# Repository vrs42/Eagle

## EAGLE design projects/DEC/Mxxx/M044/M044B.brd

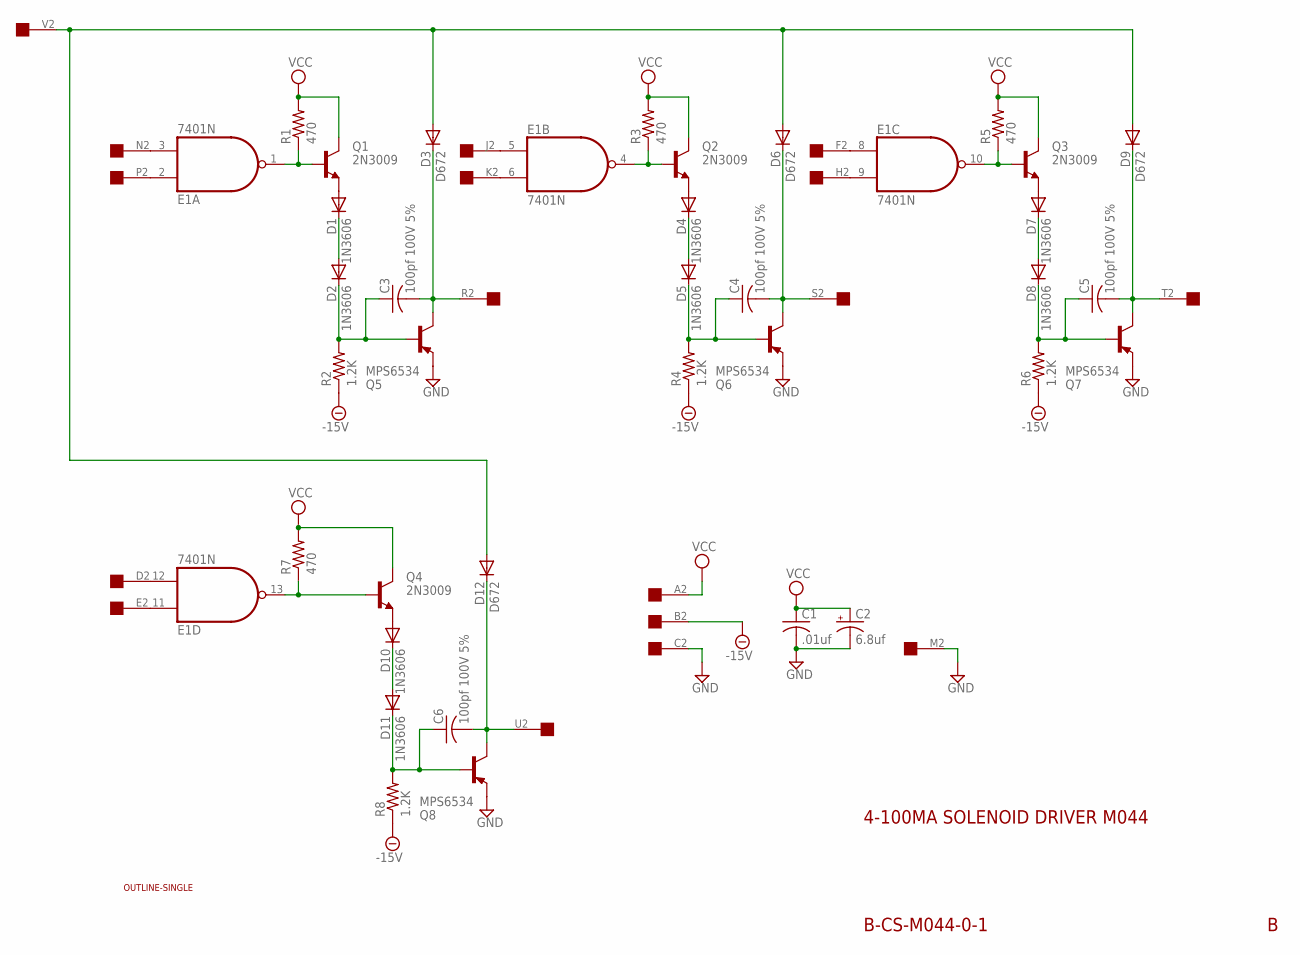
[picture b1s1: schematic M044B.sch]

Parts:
C1: .01uf; C050-025X075
C2: 6.8uf; E15-5
C3, C4, C5, C6: 100pf 100V 5%; C050-025X075
D1, D2, D4, D5, D7, D8, D10, D11: 1N3606; DO35-10
D3, D6, D9, D12: D672; DO35-10
E1: 7401N; DIL14
Q1, Q2, Q3, Q4: 2N3009; TO39
Q5, Q6, Q7, Q8: MPS6534; TO39
R1, R3, R5, R7: 470; 0207/10
R2, R4, R6, R8: 1.2K; 0207/10
U$1: OUTLINE-SINGLE; SINGLE
U$2: EDGE-1; EDGE-CON1

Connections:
-15V: R2.1, R4.1, R6.1, R8.1, U$2.B2
GND: C1.2, C2.-, E1.7 (GND), Q5.1 (E), Q6.1 (E), Q7.1 (E), Q8.1 (E), U$2.C2, U$2.M2
unnamed: E1.3 (I1), U$2.N2
unnamed: E1.2 (I0), U$2.P2
unnamed: E1.1 (O), Q1.2 (B), R1.1
unnamed: D1.A, Q1.1 (E)
unnamed: D1.C, D2.A
unnamed: C3.1, D2.C, Q5.2 (B), R2.2
unnamed: C3.2, D3.C, Q5.3 (C), U$2.R2
unnamed: D3.A, D6.A, D9.A, D12.A, U$2.V2
unnamed: E1.4 (O), Q2.2 (B), R3.1
unnamed: D4.A, Q2.1 (E)
unnamed: D4.C, D5.A
unnamed: C4.1, D5.C, Q6.2 (B), R4.2
unnamed: C4.2, D6.C, Q6.3 (C), U$2.S2
unnamed: E1.5 (I0), U$2.J2
unnamed: E1.6 (I1), U$2.K2
unnamed: E1.10 (O), Q3.2 (B), R5.1
unnamed: D7.A, Q3.1 (E)
unnamed: D7.C, D8.A
unnamed: C5.1, D8.C, Q7.2 (B), R6.2
unnamed: C5.2, D9.C, Q7.3 (C), U$2.T2
unnamed: E1.13 (O), Q4.2 (B), R7.1
unnamed: E1.9 (I1), U$2.H2
unnamed: E1.8 (I0), U$2.F2
unnamed: D10.A, Q4.1 (E)
unnamed: D10.C, D11.A
unnamed: C6.1, D11.C, Q8.2 (B), R8.2
unnamed: C6.2, D12.C, Q8.3 (C), U$2.U2
unnamed: E1.11 (I0), U$2.E2
unnamed: E1.12 (I1), U$2.D2
VCC: C1.1, C2.+, E1.14 (VCC), Q1.3 (C), Q2.3 (C), Q3.3 (C), Q4.3 (C), R1.2, R3.2, R5.2, R7.2, U$2.A2

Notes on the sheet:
4-100MA SOLENOID DRIVER M044
B-CS-M044-0-1

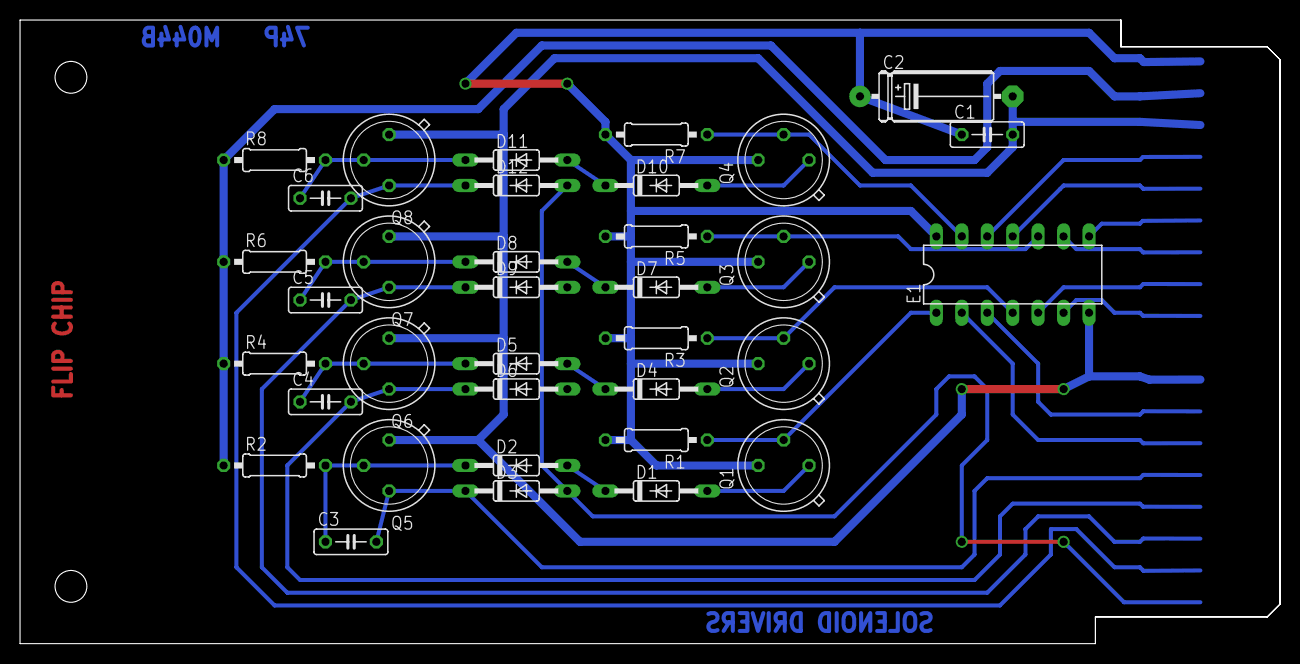
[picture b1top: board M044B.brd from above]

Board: 2 copper layers, 125.7 x 62.2 mm, 37 parts (0 on the bottom side), 32 nets.

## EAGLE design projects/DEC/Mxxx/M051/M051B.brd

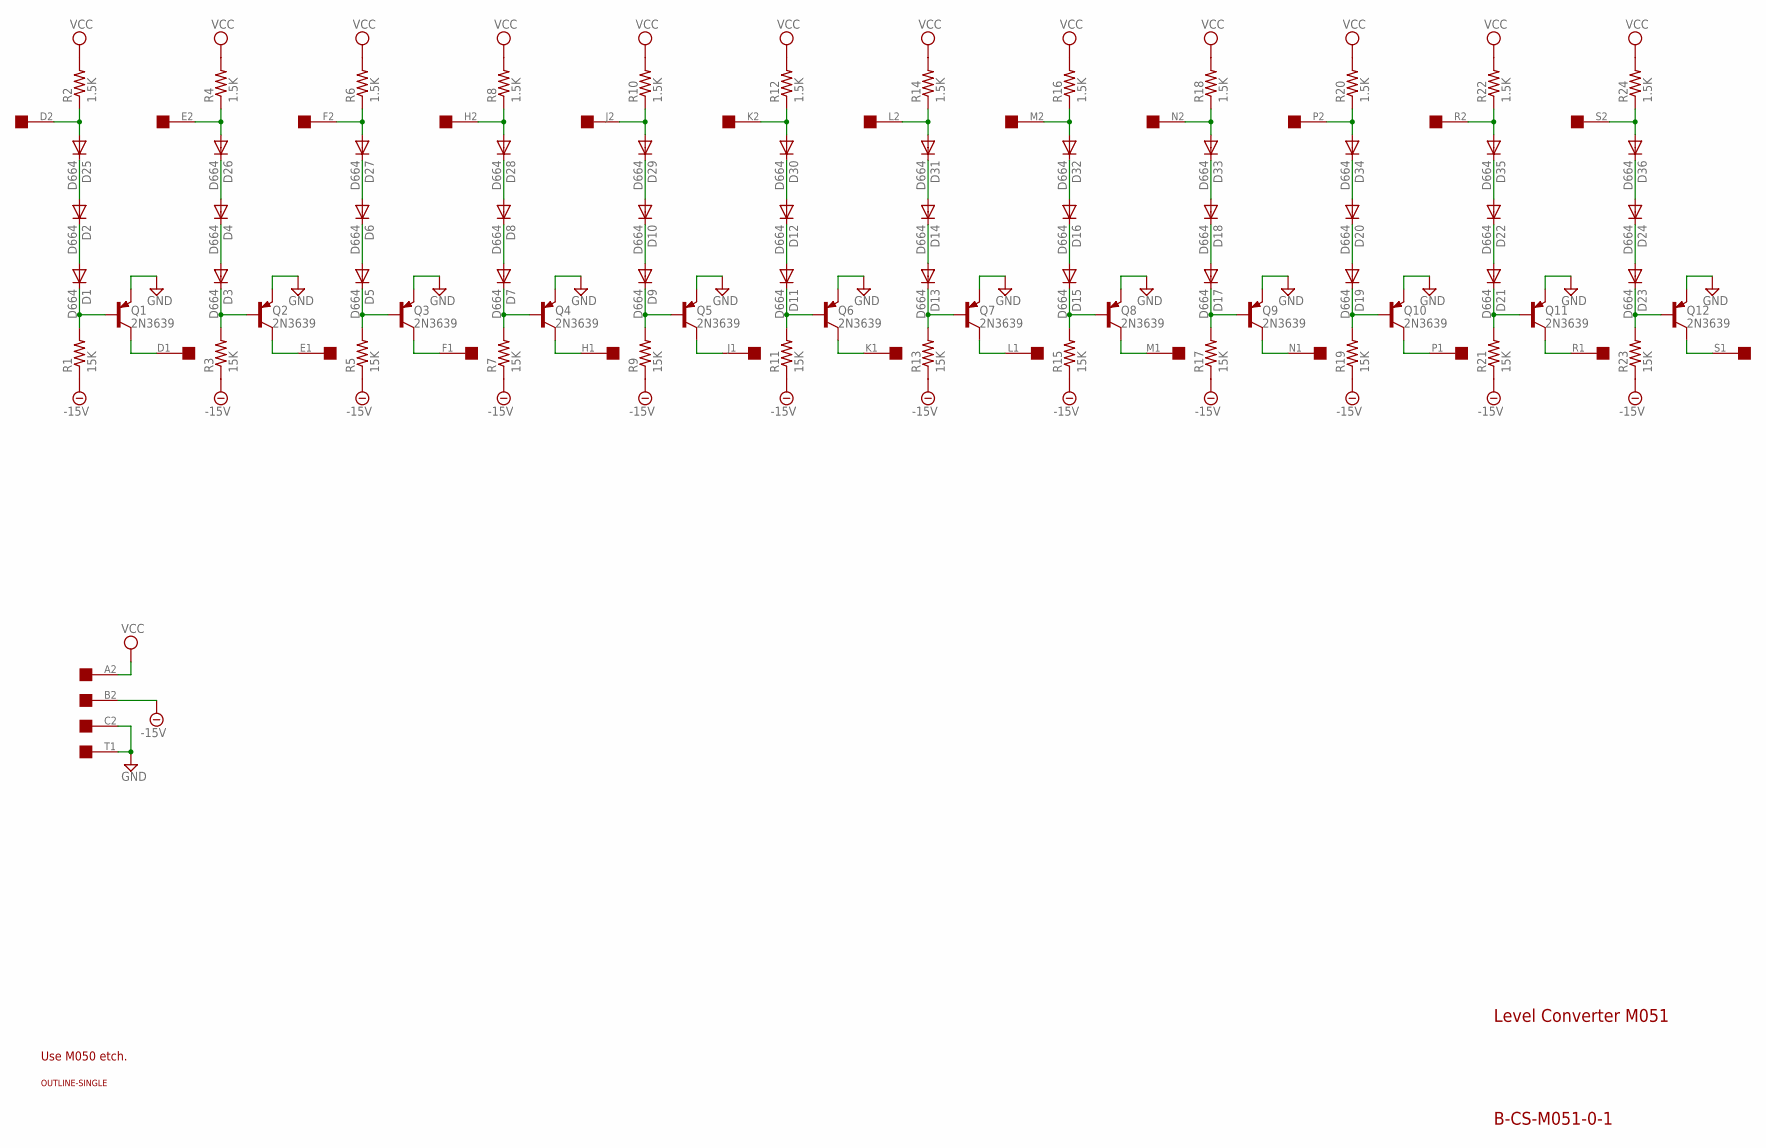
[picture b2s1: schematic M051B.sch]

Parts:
D1, D2, D3, D4, D5, D6, D7, D8, D9, D10, D11, D12, D13, D14, D15, D16, D17, D18, D19, D20, D21, D22, D23, D24, D25, D26, D27, D28, D29, D30, D31, D32, D33, D34, D35, D36: D664; DO35-10
Q1, Q2, Q3, Q4, Q5, Q6, Q7, Q8, Q9, Q10, Q11, Q12: 2N3639; TO5
R1, R3, R5, R7, R9, R11, R13, R15, R17, R19, R21, R23: 15K; 0207/10
R2, R4, R6, R8, R10, R12, R14, R16, R18, R20, R22, R24: 1.5K; 0207/10
U$1: OUTLINE-SINGLE; SINGLE
U$2: SINGLE; EDGE-CON2

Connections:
-15V: R1.1, R3.1, R5.1, R7.1, R9.1, R11.1, R13.1, R15.1, R17.1, R19.1, R21.1, R23.1, U$2.B2
D7: D6.A, D27.C
GND: Q1.1 (E), Q2.1 (E), Q3.1 (E), Q4.1 (E), Q5.1 (E), Q6.1 (E), Q7.1 (E), Q8.1 (E), Q9.1 (E), Q10.1 (E), Q11.1 (E), Q12.1 (E), U$2.C2, U$2.T1
unnamed: D25.A, R2.1, U$2.D2
unnamed: D2.A, D25.C
unnamed: D1.A, D2.C
unnamed: D1.C, Q1.2 (B), R1.2
unnamed: Q1.3 (C), U$2.D1
unnamed: D26.A, R4.1, U$2.E2
unnamed: D4.A, D26.C
unnamed: D3.A, D4.C
unnamed: D3.C, Q2.2 (B), R3.2
unnamed: Q2.3 (C), U$2.E1
unnamed: D27.A, R6.1, U$2.F2
unnamed: D5.A, D6.C
unnamed: D5.C, Q3.2 (B), R5.2
unnamed: Q3.3 (C), U$2.F1
unnamed: D28.A, R8.1, U$2.H2
unnamed: D8.A, D28.C
unnamed: D7.A, D8.C
unnamed: D7.C, Q4.2 (B), R7.2
unnamed: Q4.3 (C), U$2.H1
unnamed: D29.A, R10.1, U$2.J2
unnamed: D10.A, D29.C
unnamed: D9.A, D10.C
unnamed: D9.C, Q5.2 (B), R9.2
unnamed: Q5.3 (C), U$2.J1
unnamed: D30.A, R12.1, U$2.K2
unnamed: D12.A, D30.C
unnamed: D11.A, D12.C
unnamed: D11.C, Q6.2 (B), R11.2
unnamed: Q6.3 (C), U$2.K1
unnamed: D31.A, R14.1, U$2.L2
unnamed: D14.A, D31.C
unnamed: D13.A, D14.C
unnamed: D13.C, Q7.2 (B), R13.2
unnamed: Q7.3 (C), U$2.L1
unnamed: D32.A, R16.1, U$2.M2
unnamed: D16.A, D32.C
unnamed: D15.A, D16.C
unnamed: D15.C, Q8.2 (B), R15.2
unnamed: Q8.3 (C), U$2.M1
unnamed: D33.A, R18.1, U$2.N2
unnamed: D18.A, D33.C
unnamed: D17.A, D18.C
unnamed: D17.C, Q9.2 (B), R17.2
unnamed: Q9.3 (C), U$2.N1
unnamed: D34.A, R20.1, U$2.P2
unnamed: D20.A, D34.C
unnamed: D19.A, D20.C
unnamed: D19.C, Q10.2 (B), R19.2
unnamed: Q10.3 (C), U$2.P1
unnamed: D35.A, R22.1, U$2.R2
unnamed: D22.A, D35.C
unnamed: D21.A, D22.C
unnamed: D21.C, Q11.2 (B), R21.2
unnamed: Q11.3 (C), U$2.R1
unnamed: D36.A, R24.1, U$2.S2
unnamed: D24.A, D36.C
unnamed: D23.A, D24.C
unnamed: D23.C, Q12.2 (B), R23.2
unnamed: Q12.3 (C), U$2.S1
VCC: R2.2, R4.2, R6.2, R8.2, R10.2, R12.2, R14.2, R16.2, R18.2, R20.2, R22.2, R24.2, U$2.A2

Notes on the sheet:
Level Converter M051
B-CS-M051-0-1
Use M050 etch.

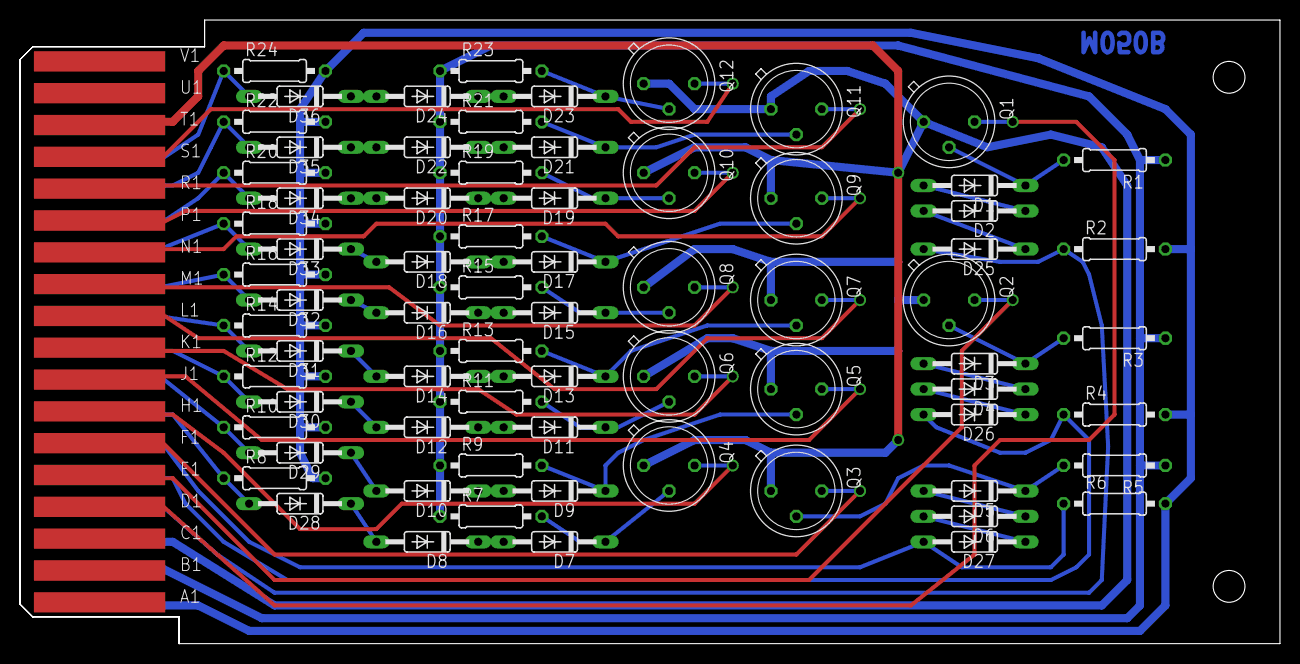
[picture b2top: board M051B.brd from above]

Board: 2 copper layers, 125.7 x 62.2 mm, 74 parts (0 on the bottom side), 63 nets.

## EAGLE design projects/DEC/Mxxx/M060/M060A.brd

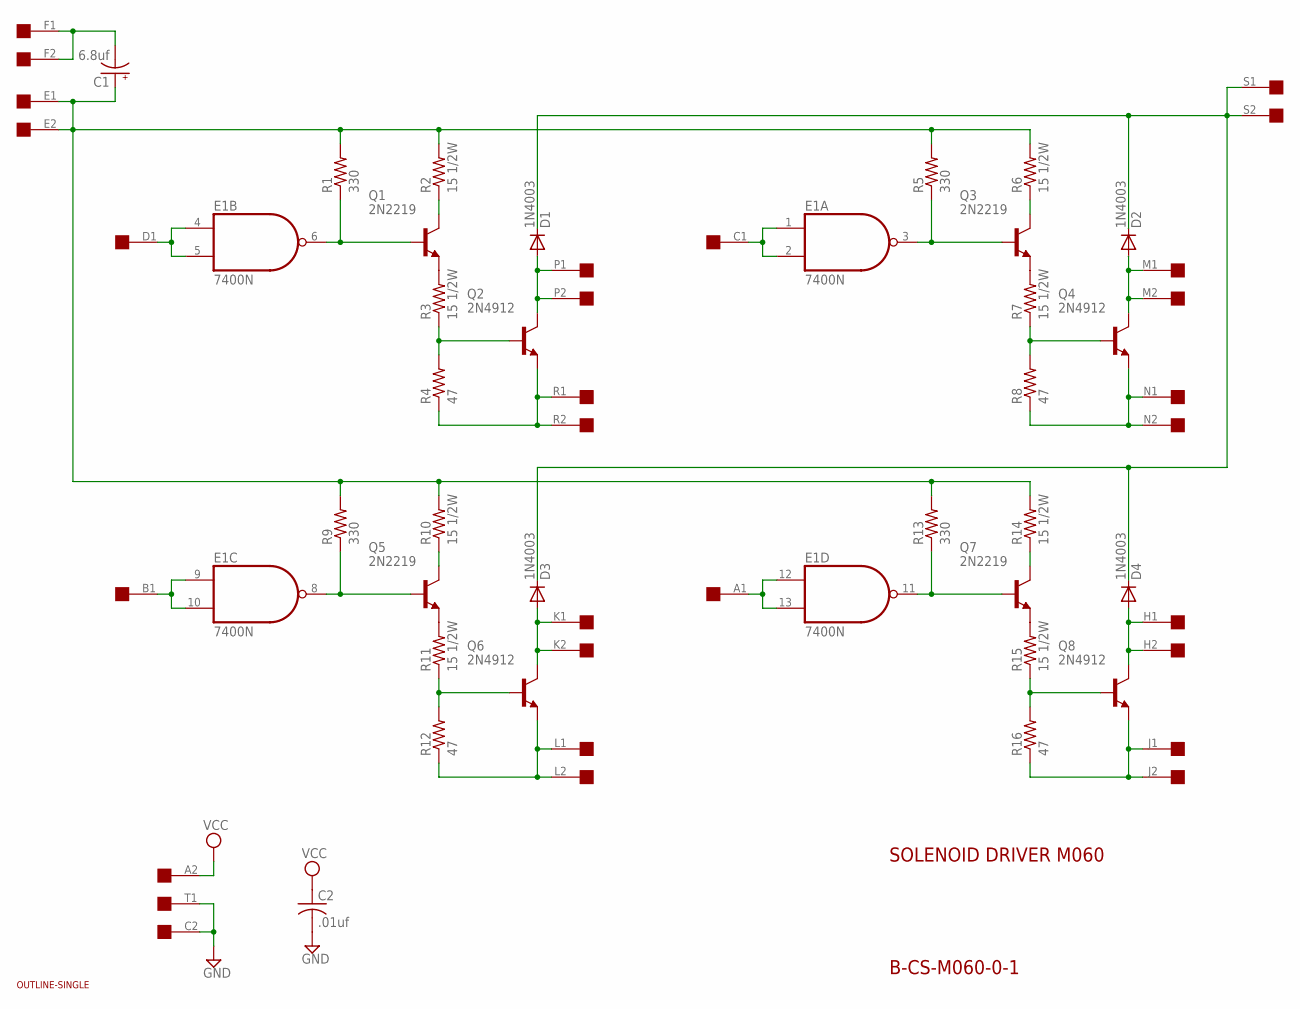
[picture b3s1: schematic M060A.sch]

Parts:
C1: 6.8uf; E15-5
C2: .01uf; C050-025X075
D1, D2, D3, D4: 1N4003; DO41-10
E1: 7400N; DIL14
Q1, Q3, Q5, Q7: 2N2219; TO5
Q2, Q4, Q6, Q8: 2N4912; TO66
R1, R5, R9, R13: 330; 0207/10
R2, R3, R6, R7, R10, R11, R14, R15: 15 1/2W; 0411/15
R4, R8, R12, R16: 47; 0207/10
U$1: SINGLE; EDGE-CON2
U$2: OUTLINE-SINGLE; SINGLE

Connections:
GND: C2.2, E1.7 (GND), U$1.C2, U$1.T1
unnamed: E1.4 (I0), E1.5 (I1), U$1.D1
unnamed: E1.6 (O), Q1.2 (B), R1.1
unnamed: C1.+, R1.2, R2.2, R5.2, R6.2, R9.2, R10.2, R13.2, R14.2, U$1.E1, U$1.E2
unnamed: Q1.3 (C), R2.1
unnamed: Q1.1 (E), R3.2
unnamed: Q2.2 (B), R3.1, R4.2
unnamed: Q2.1 (E), R4.1, U$1.R1, U$1.R2
unnamed: D1.A, Q2.3 (C), U$1.P1, U$1.P2
unnamed: D1.C, D2.C, D3.C, D4.C, U$1.S1, U$1.S2
unnamed: E1.1 (I0), E1.2 (I1), U$1.C1
unnamed: E1.3 (O), Q3.2 (B), R5.1
unnamed: Q3.3 (C), R6.1
unnamed: Q3.1 (E), R7.2
unnamed: Q4.2 (B), R7.1, R8.2
unnamed: Q4.1 (E), R8.1, U$1.N1, U$1.N2
unnamed: D2.A, Q4.3 (C), U$1.M1, U$1.M2
unnamed: E1.9 (I0), E1.10 (I1), U$1.B1
unnamed: E1.8 (O), Q5.2 (B), R9.1
unnamed: C1.-, U$1.F1, U$1.F2
unnamed: Q5.3 (C), R10.1
unnamed: Q5.1 (E), R11.2
unnamed: Q6.2 (B), R11.1, R12.2
unnamed: Q6.1 (E), R12.1, U$1.L1, U$1.L2
unnamed: D3.A, Q6.3 (C), U$1.K1, U$1.K2
unnamed: E1.12 (I0), E1.13 (I1), U$1.A1
unnamed: E1.11 (O), Q7.2 (B), R13.1
unnamed: Q7.3 (C), R14.1
unnamed: Q7.1 (E), R15.2
unnamed: Q8.2 (B), R15.1, R16.2
unnamed: Q8.1 (E), R16.1, U$1.J1, U$1.J2
unnamed: D4.A, Q8.3 (C), U$1.H1, U$1.H2
VCC: C2.1, E1.14 (VCC), U$1.A2

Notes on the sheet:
SOLENOID DRIVER M060
B-CS-M060-0-1

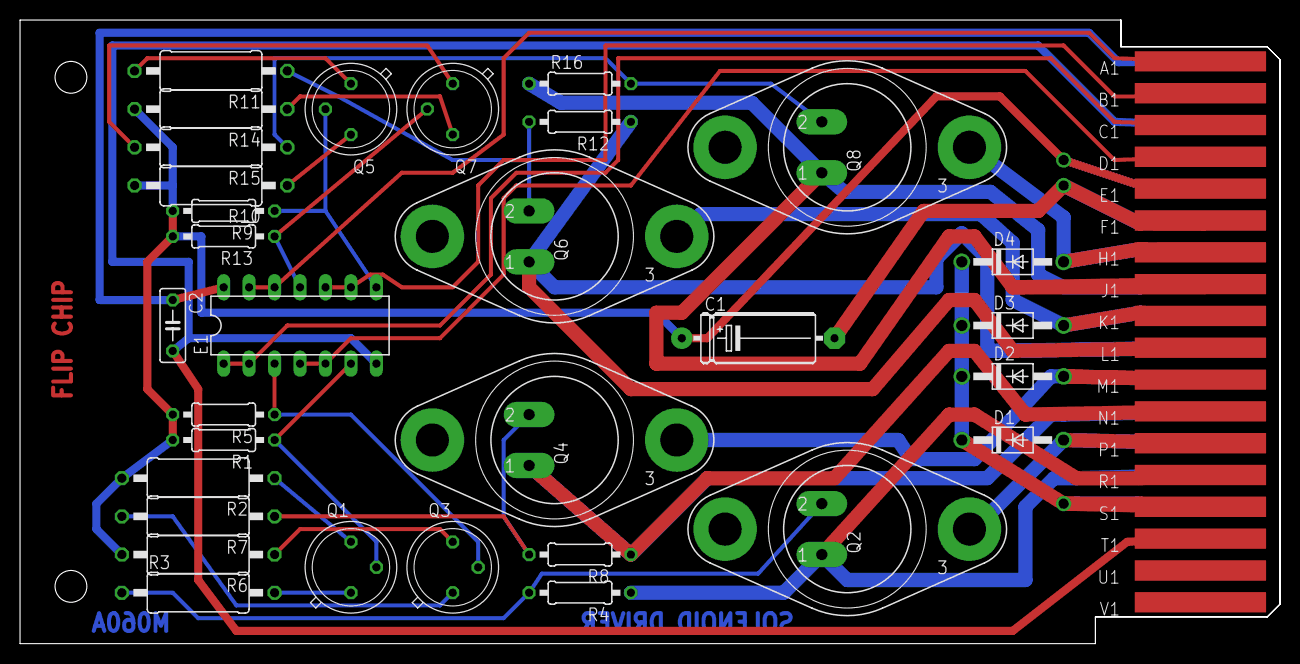
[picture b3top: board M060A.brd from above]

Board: 2 copper layers, 125.7 x 62.2 mm, 33 parts (0 on the bottom side), 33 nets.

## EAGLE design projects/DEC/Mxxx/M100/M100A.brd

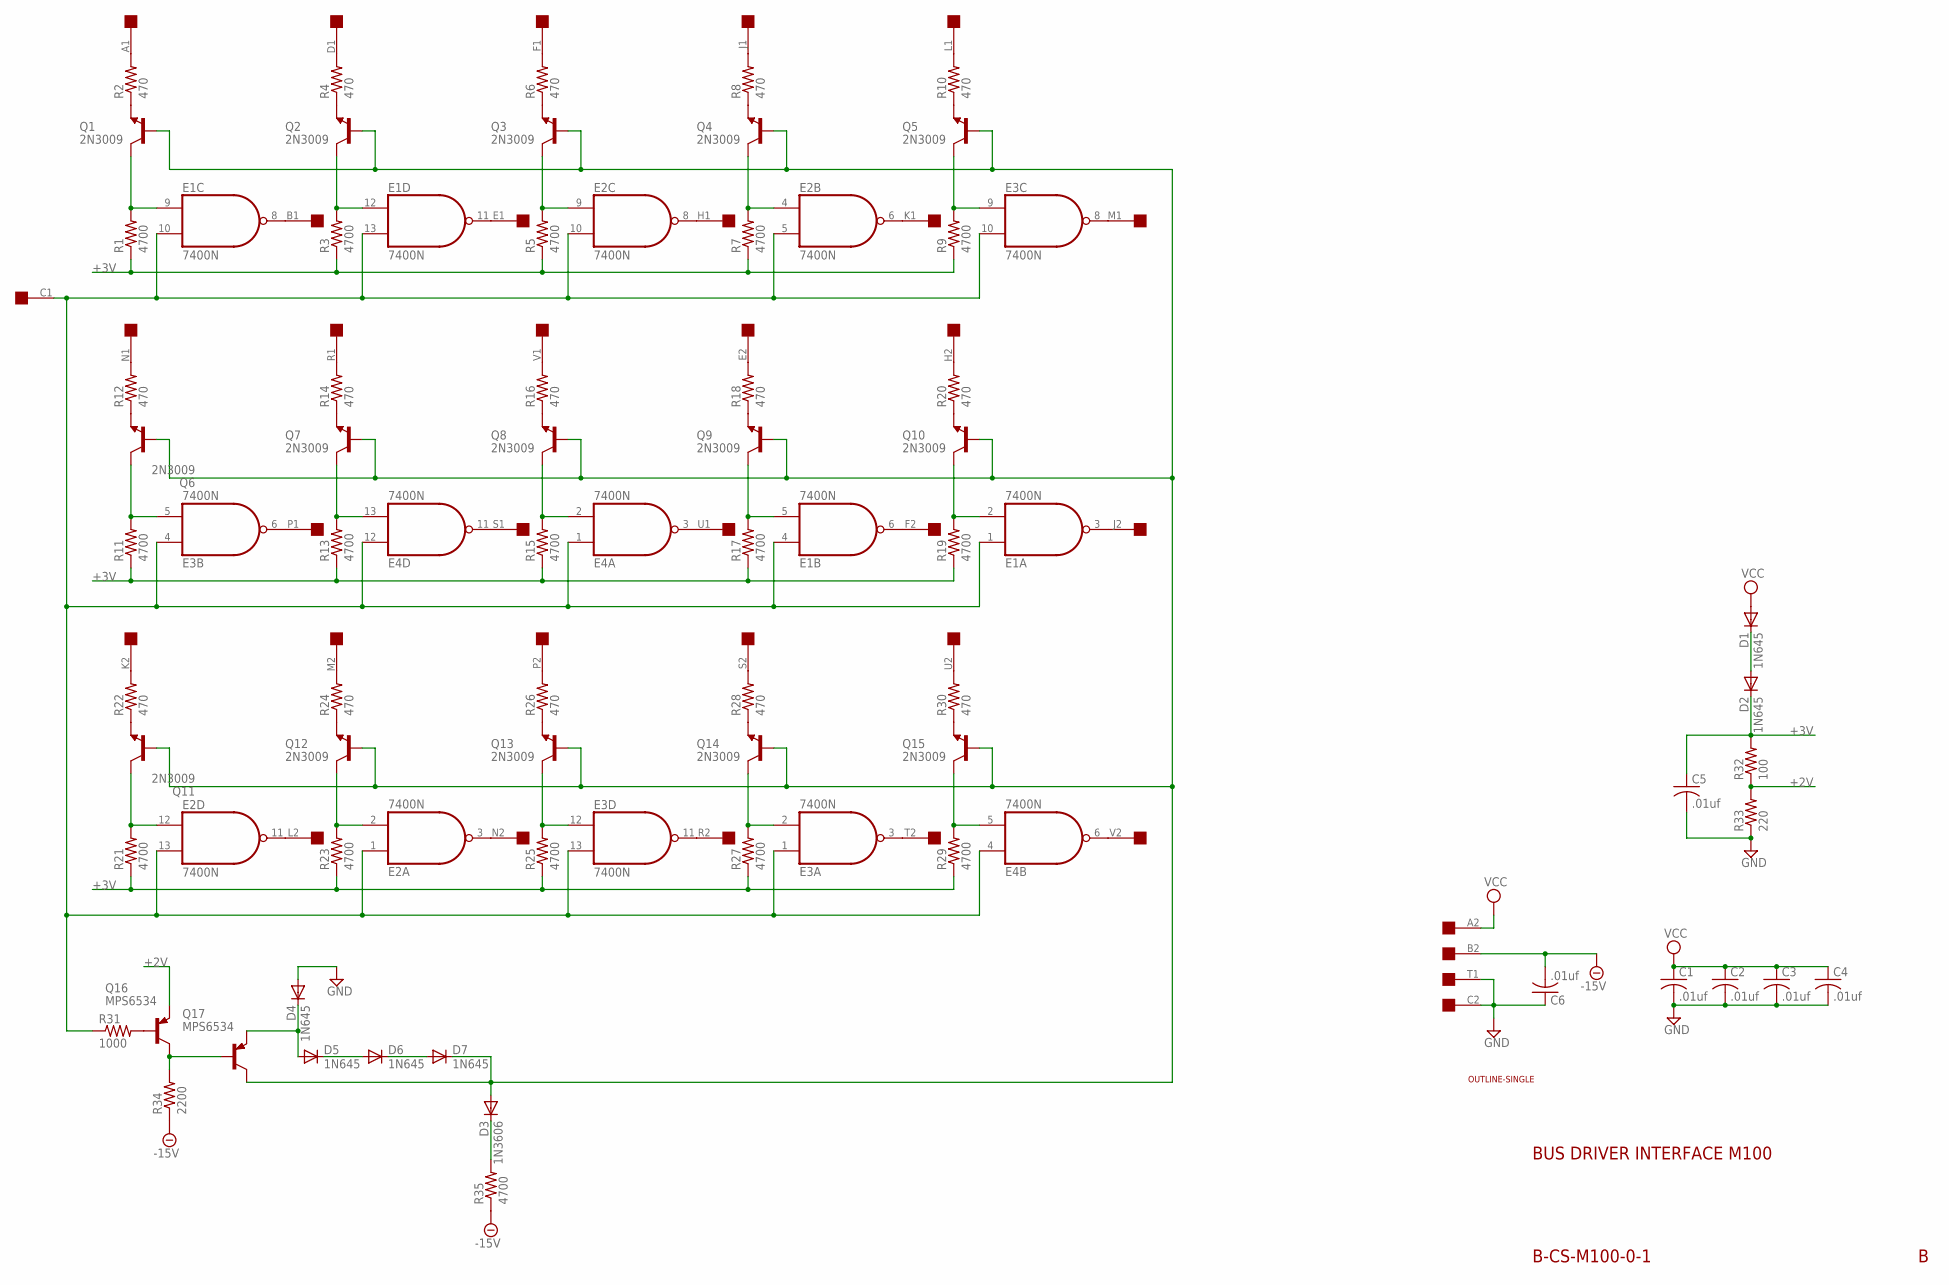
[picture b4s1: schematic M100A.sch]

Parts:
C1, C2, C3, C4, C5, C6: .01uf; C050-025X075
D1, D2, D4, D5, D6, D7: 1N645; DO35-10
D3: 1N3606; DO35-10
E1, E2, E3, E4: 7400N; DIL14
Q1, Q2, Q3, Q4, Q5, Q6, Q7, Q8, Q9, Q10, Q11, Q12, Q13, Q14, Q15: 2N3009; TO5
Q16, Q17: MPS6534; TO5
R1, R3, R5, R7, R9, R11, R13, R15, R17, R19, R21, R23, R25, R27, R29, R35: 4700; 0207/10
R2, R4, R6, R8, R10, R12, R14, R16, R18, R20, R22, R24, R26, R28, R30: 470; 0207/10
R31: 1000; 0207/10
R32: 100; 0207/10
R33: 220; 0207/10
R34: 2200; 0207/10
U$1: SINGLE; EDGE-CON2
U$2: OUTLINE-SINGLE; SINGLE

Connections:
+2V: Q16.1 (E), R32.1, R33.2
+3V: C5.1, D2.C, R1.1, R3.1, R5.1, R7.1, R9.1, R11.1, R13.1, R15.1, R17.1, R19.1, R21.1, R23.1, R25.1, R27.1, R29.1, R32.2
-15V: C6.2, R34.1, R35.1, U$1.B2
GND: C1.2, C2.2, C3.2, C4.2, C5.2, C6.1, D4.A, E1.7 (GND), E2.7 (GND), E3.7 (GND), E4.7 (GND), R33.1, U$1.C2, U$1.T1
unnamed: Q1.1 (E), R2.1
unnamed: E1.9 (I0), Q1.3 (C), R1.2
unnamed: E1.1 (I0), E1.4 (I0), E1.10 (I1), E1.13 (I1), E2.1 (I0), E2.5 (I1), E2.10 (I1), E2.13 (I1), E3.1 (I0), E3.4 (I0), E3.10 (I1), E3.13 (I1), E4.1 (I0), E4.4 (I0), E4.12 (I0), R31.1, U$1.C1
unnamed: E1.12 (I0), Q2.3 (C), R3.2
unnamed: E1.8 (O), U$1.B1
unnamed: Q2.1 (E), R4.1
unnamed: R4.2, U$1.D1
unnamed: E1.11 (O), U$1.E1
unnamed: R6.2, U$1.F1
unnamed: Q3.1 (E), R6.1
unnamed: E2.9 (I0), Q3.3 (C), R5.2
unnamed: E2.8 (O), U$1.H1
unnamed: R8.2, U$1.J1
unnamed: Q4.1 (E), R8.1
unnamed: E2.4 (I0), Q4.3 (C), R7.2
unnamed: E2.6 (O), U$1.K1
unnamed: R10.2, U$1.L1
unnamed: E3.8 (O), U$1.M1
unnamed: E3.9 (I0), Q5.3 (C), R9.2
unnamed: Q5.1 (E), R10.1
unnamed: D3.A, D7.C, Q1.2 (B), Q2.2 (B), Q3.2 (B), Q4.2 (B), Q5.2 (B), Q6.2 (B), Q7.2 (B), Q8.2 (B), Q9.2 (B), Q10.2 (B), Q11.2 (B), Q12.2 (B), Q13.2 (B), Q14.2 (B), Q15.2 (B), Q17.3 (C)
unnamed: R12.2, U$1.N1
unnamed: Q6.1 (E), R12.1
unnamed: E3.5 (I1), Q6.3 (C), R11.2
unnamed: E3.6 (O), U$1.P1
unnamed: E4.11 (O), U$1.S1
unnamed: Q7.1 (E), R14.1
unnamed: R14.2, U$1.R1
unnamed: E4.13 (I1), Q7.3 (C), R13.2
unnamed: E4.3 (O), U$1.U1
unnamed: R16.2, U$1.V1
unnamed: R2.2, U$1.A1
unnamed: E4.2 (I1), Q8.3 (C), R15.2
unnamed: R18.2, U$1.E2
unnamed: E1.6 (O), U$1.F2
unnamed: R20.2, U$1.H2
unnamed: Q8.1 (E), R16.1
unnamed: Q9.1 (E), R18.1
unnamed: E1.5 (I1), Q9.3 (C), R17.2
unnamed: E1.3 (O), U$1.J2
unnamed: R22.2, U$1.K2
unnamed: E1.2 (I1), Q10.3 (C), R19.2
unnamed: Q10.1 (E), R20.1
unnamed: Q11.1 (E), R22.1
unnamed: E2.12 (I0), Q11.3 (C), R21.2
unnamed: E2.11 (O), U$1.L2
unnamed: R24.2, U$1.M2
unnamed: Q12.1 (E), R24.1
unnamed: E2.3 (O), U$1.N2
unnamed: E2.2 (I1), Q12.3 (C), R23.2
unnamed: R26.2, U$1.P2
unnamed: E3.11 (O), U$1.R2
unnamed: E3.12 (I0), Q13.3 (C), R25.2
unnamed: R28.2, U$1.S2
unnamed: E3.3 (O), U$1.T2
unnamed: R30.2, U$1.U2
unnamed: Q13.1 (E), R26.1
unnamed: Q14.1 (E), R28.1
unnamed: E3.2 (I1), Q14.3 (C), R27.2
unnamed: E4.6 (O), U$1.V2
unnamed: D1.C, D2.A
unnamed: E4.5 (I1), Q15.3 (C), R29.2
unnamed: Q15.1 (E), R30.1
unnamed: D3.C, R35.2
unnamed: D5.C, D6.A
unnamed: D6.C, D7.A
unnamed: Q16.2 (B), R31.2
unnamed: Q16.3 (C), Q17.2 (B), R34.2
unnamed: D4.C, D5.A, Q17.1 (E)
VCC: C1.1, C2.1, C3.1, C4.1, D1.A, E1.14 (VCC), E2.14 (VCC), E3.14 (VCC), E4.14 (VCC), U$1.A2

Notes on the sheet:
BUS DRIVER INTERFACE M100
B-CS-M100-0-1

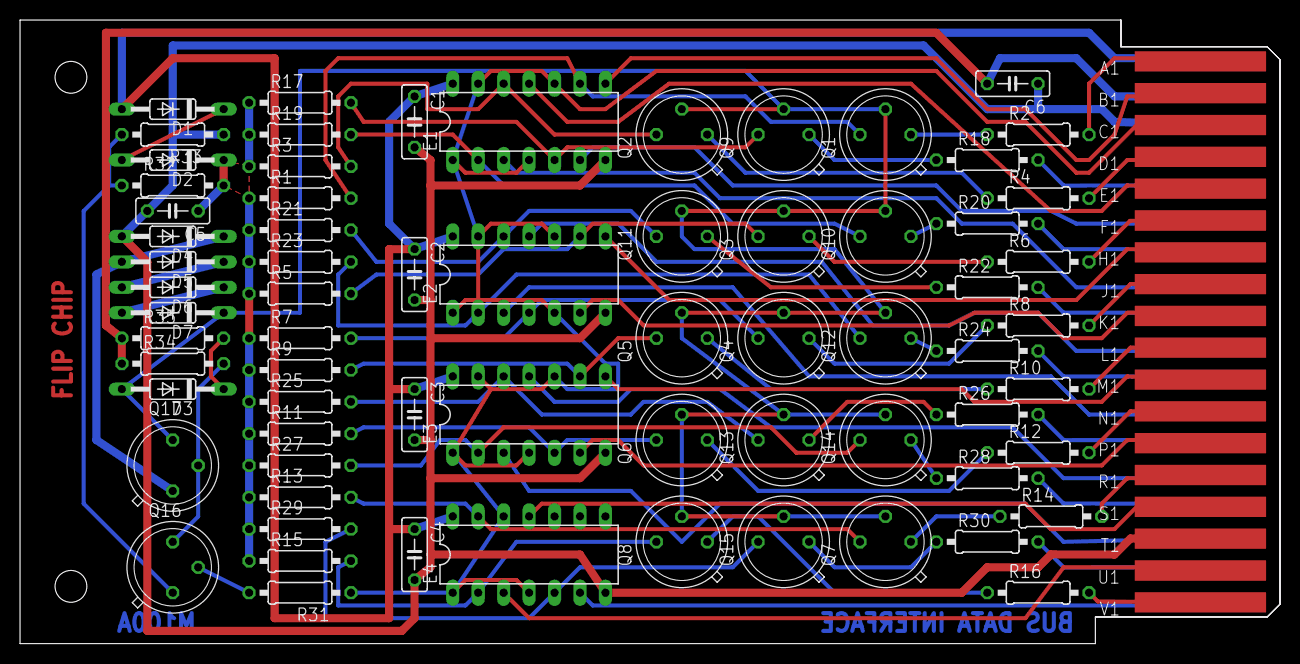
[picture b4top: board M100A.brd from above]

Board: 2 copper layers, 125.7 x 62.2 mm, 71 parts (0 on the bottom side), 74 nets.
